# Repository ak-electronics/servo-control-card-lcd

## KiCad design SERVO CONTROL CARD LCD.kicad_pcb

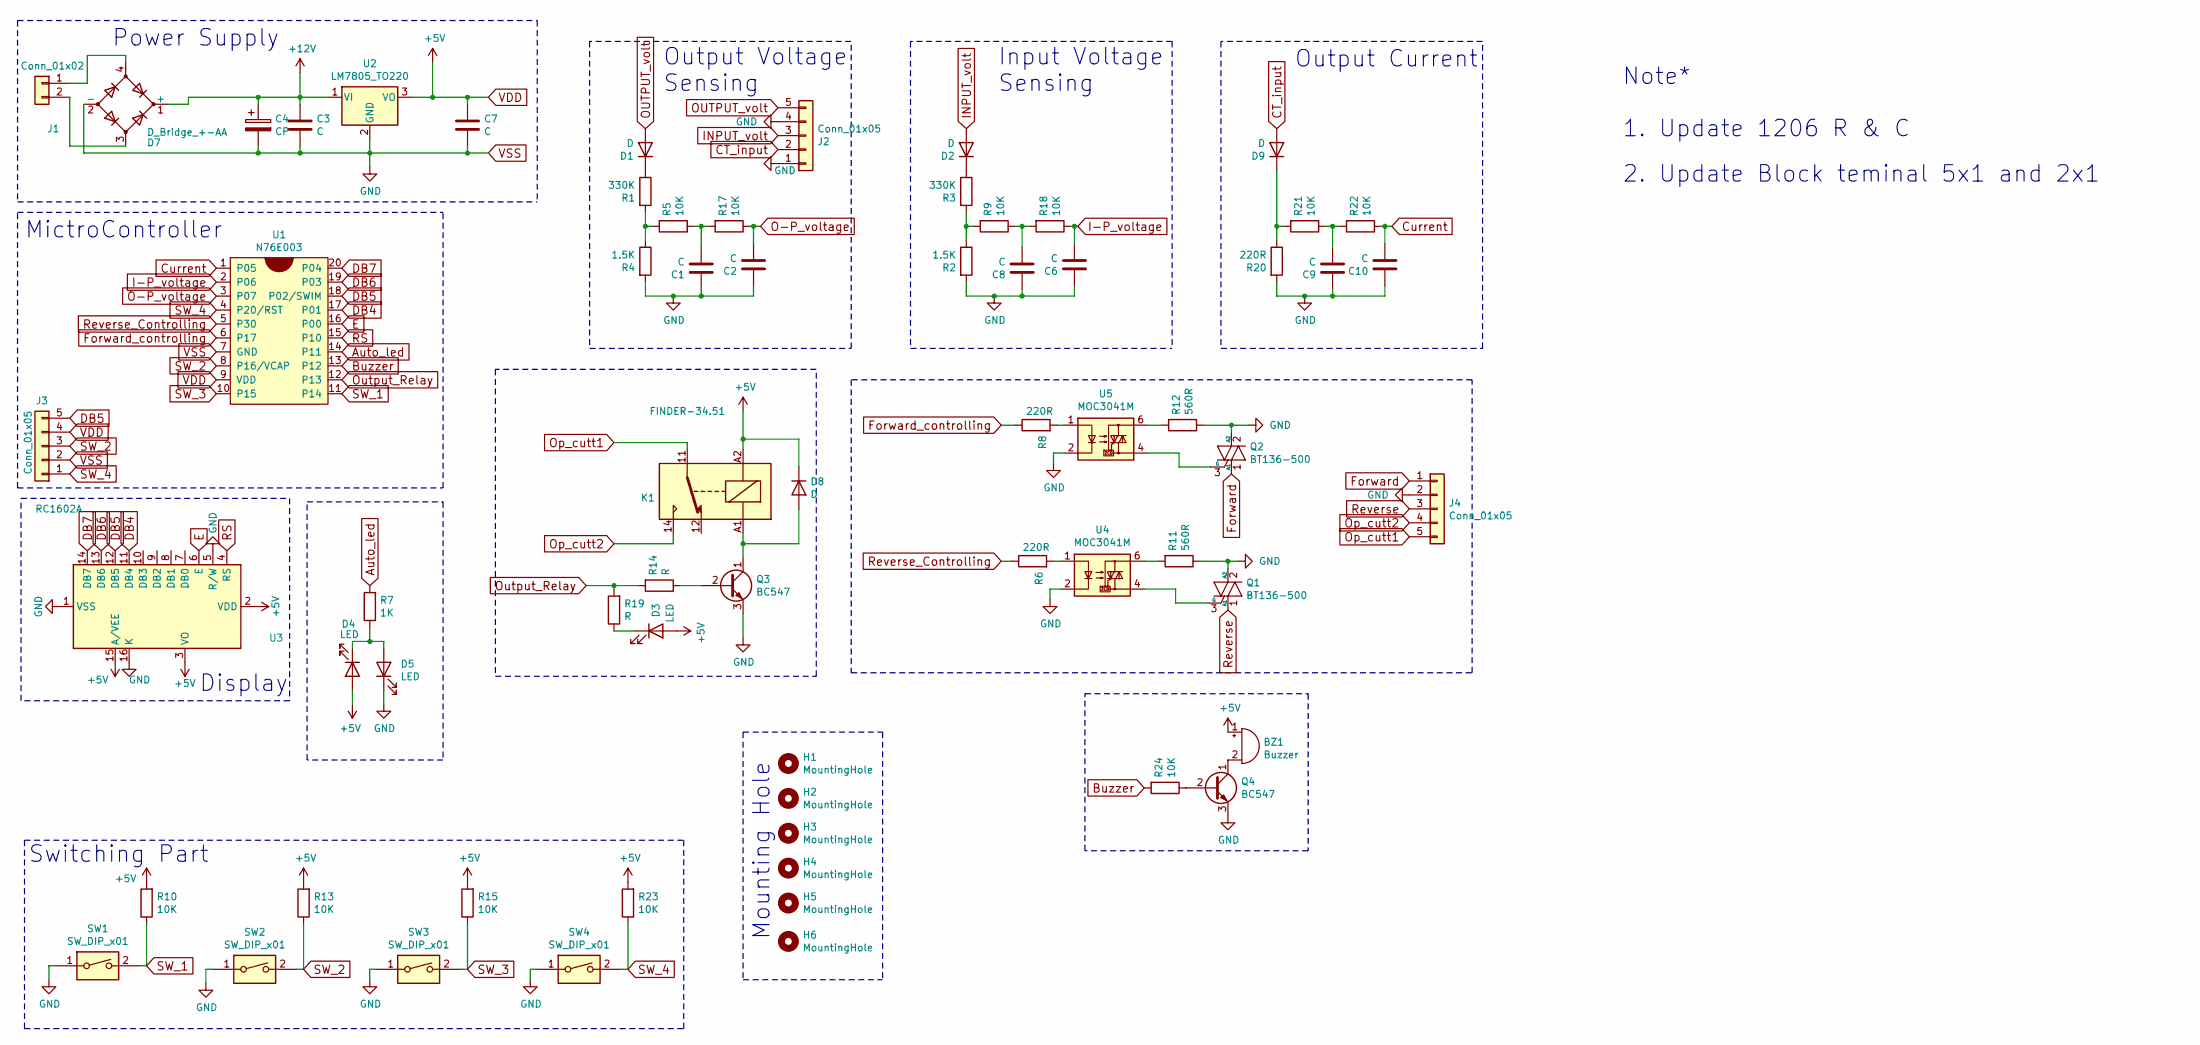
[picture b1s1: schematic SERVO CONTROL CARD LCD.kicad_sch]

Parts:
BZ1: Buzzer; Buzzer_12x9.5RM7.6
C1, C2, C3, C6, C7, C8, C9, C10: C; C_1206_3216Metric
C4: CP; CP_Radial_D8.0mm_P5.00mm
D1, D2, D8, D9: D; D_1206
D3, D4, D5: LED; LED_D3.0mm
D7: D_Bridge_+-AA; MB10_bridge
H1, H2, H3, H4, H5, H6: MountingHole; MountingHole_3.2mm_M3_Pad_Via
J1: Conn_01x02; Block_connector_2x1_H1.5_P8
J2, J4: Conn_01x05; Block_connector_5x1_H1.5_P8
J3: Conn_01x05; 5_Pin_PinHeader_1x05_P2.54mm_Vertical
K1: FINDER-34.51; Relay_SPDT_Finder_36.11
Q1, Q2: BT136-500; TO-220-3_Vertical
Q3, Q4: BC547; SOT-23_Transistor
R1, R3: 330K; R_1206_3216Metric
R2, R4: 1.5K; R_1206_3216Metric
R5, R9, R10, R13, R15, R17, R18, R21, R22, R23, R24: 10K; R_1206_3216Metric
R6, R8, R20: 220R; R_1206_3216Metric
R7: 1K; R_1206_3216Metric
R11, R12: 560R; R_1206_3216Metric
R14, R19: R; R_1206_3216Metric
SW1, SW2, SW3, SW4: SW_DIP_x01; SW_PUSH-12mm
U1: N76E003; SSOP-20_5.3x7.2mm_P0.65mm
U2: LM7805_TO220; TO-126_Horizontal_7805
U3: RC1602A; WC1602A
U4, U5: MOC3041M; DIP-6_W7.62mm_Socket_LongPads

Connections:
+12V: C3.2, C4.1, D7.1 (+), U2.1 (VI)
Auto_led: R7.2, U1.14 (P11)
Buzzer: R24.2, U1.13 (P12)
CT_input: D9.2 (A), J2.2
Current: C10.1, R22.1, U1.1 (P05)
DB4: U1.17 (P01), U3.11 (DB4)
DB5: J3.5, U1.18 (P02/SWIM), U3.12 (DB5)
DB6: U1.19 (P03), U3.13 (DB6)
DB7: U1.20 (P04), U3.14 (DB7)
E: U1.16 (P00), U3.6 (E)
Forward: J4.1, Q2.1 (A1)
Forward_controlling: R8.1, U1.6 (P17)
I-P_voltage: C6.1, R18.1, U1.2 (P06)
INPUT_volt: D2.2 (A), J2.3
unnamed: BZ1.2 (-), Q4.1 (C)
unnamed: C1.1, R5.1, R17.2
unnamed: C8.1, R9.1, R18.2
unnamed: C9.1, R21.1, R22.2
unnamed: D1.1 (K), R1.1
unnamed: D2.1 (K), R3.1
unnamed: D3.2 (K), R19.1
unnamed: D4.2 (K), D5.1 (A), R7.1
unnamed: D7.3, J1.2
unnamed: D7.4, J1.1
unnamed: D8.2 (A), K1.A1, Q3.1 (C)
unnamed: D9.1 (K), R20.1, R21.2
unnamed: Q1.3 (G), U4.4
unnamed: Q2.3 (G), U5.4
unnamed: Q3.2 (B), R14.1
unnamed: Q4.2 (B), R24.1
unnamed: R1.2, R4.1, R5.2
unnamed: R2.1, R3.2, R9.2
unnamed: R6.2, U4.1
unnamed: R8.2, U5.1
unnamed: R11.2, U4.6
unnamed: R12.2, U5.6
O-P_voltage: C2.1, R17.1, U1.3 (P07)
OUTPUT_volt: D1.2 (A), J2.5
Op_cutt1: J4.5, K1.11
Op_cutt2: J4.4, K1.14
Output_Relay: R14.2, R19.2, U1.12 (P13)
RS: U1.15 (P10), U3.4 (RS)
Reverse: J4.3, Q1.1 (A1)
Reverse_Controlling: R6.1, U1.5 (P30)
SW_1: R10.1, SW1.2, U1.11 (P14)
SW_2: J3.3, R13.1, SW2.2, U1.8 (P16/VCAP)
SW_3: R15.1, SW3.2, U1.10 (P15)
SW_4: J3.1, R23.1, SW4.2, U1.4 (P20/RST)
VDD: BZ1.1 (+), C7.2, D3.1 (A), D4.1 (A), D8.1 (K), J3.4, K1.A2, R10.2, R13.2, R15.2, R23.2, U1.9 (VDD), U2.3 (VO), U3.2 (VDD), U3.3 (VO), U3.15 (A/VEE)
VSS: C1.2, C2.2, C3.1, C4.2, C6.2, C7.1, C8.2, C9.2, C10.2, D5.2 (K), D7.2 (-), J2.1, J2.4, J3.2, J4.2, Q1.2 (A2), Q2.2 (A2), Q3.3 (E), Q4.3 (E), R2.2, R4.2, R11.1, R12.1, R20.2, SW1.1, SW2.1, SW3.1, SW4.1, U1.7 (GND), U2.2 (GND), U3.1 (VSS), U3.5 (R/W), U3.16 (K), U4.2, U5.2

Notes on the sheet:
Power Supply
Switching Part
1. Update 1206 R & C
Mounting Hole
Output Current
Note*
2. Update Block teminal 5x1 and 2x1
MictroController
Output Voltage Sensing
Display
Input Voltage Sensing

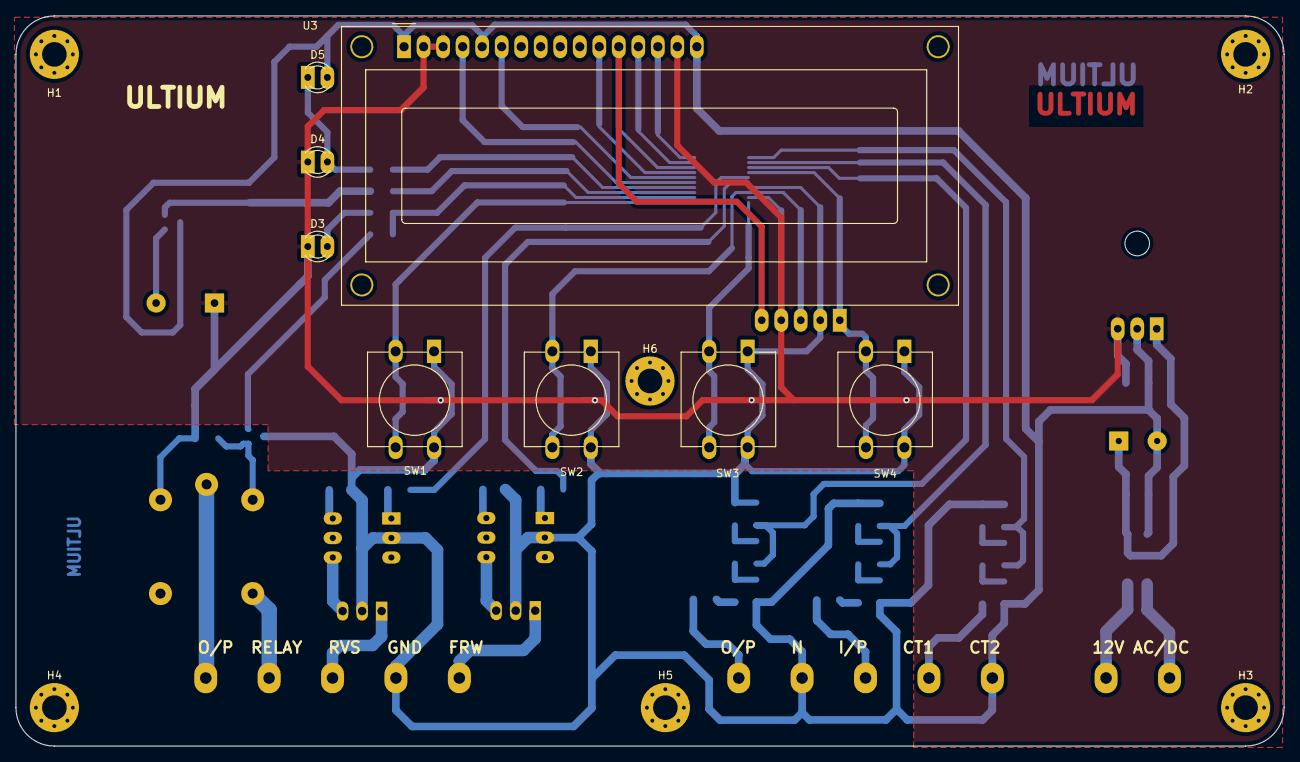
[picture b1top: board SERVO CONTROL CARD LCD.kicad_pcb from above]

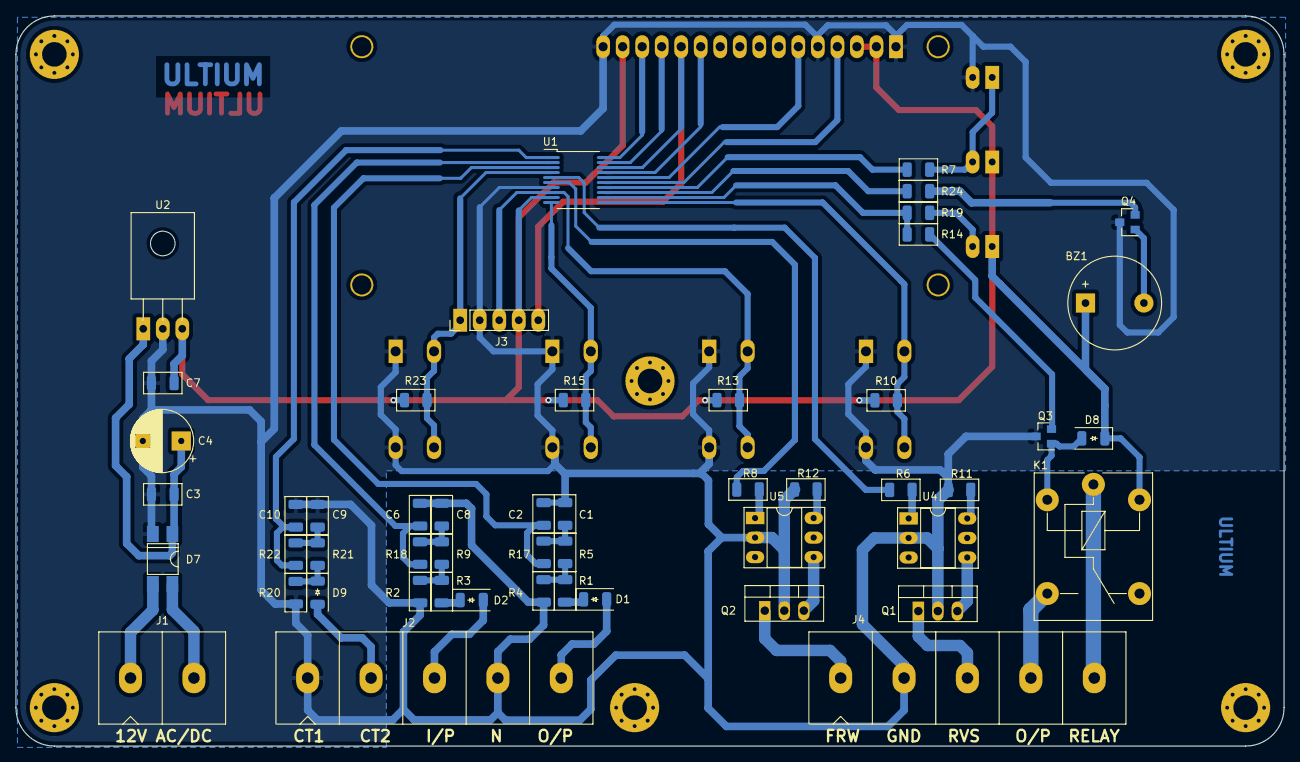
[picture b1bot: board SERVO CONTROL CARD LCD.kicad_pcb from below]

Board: 2 copper layers, 165.0 x 95.0 mm, 65 parts (51 on the bottom side), 50 nets.

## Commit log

2024-12-08 first version v1.0
2024-12-08 pcb board hase standard size
2024-12-08 pcb board hase standard size with block connector v1.2
